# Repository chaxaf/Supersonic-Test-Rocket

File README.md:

# Hermes II Avionics Redesign

Semester project completed with the EPFL Rocket Team in 2022.

Hermes II is a compact avionics architecture developed for a small experimental rocket intended for validation flights and data generation. The project focused on redesigning the electronics of the original Hermes platform into a smaller, more modular system with telemetry, GPS, multiple sensor boards, and improved integration inside the rocket.

## Project summary

The avionics stack is built around one main PCB and three auxiliary PCBs placed in different parts of the rocket:

- **Main PCB** in the avionics bay
- **Nosecone PCB** for total pressure and wall temperature
- **Static port PCB** for static pressure and wall temperature
- **Load cell PCB** for thrust measurement signal conditioning

The design integrates:
- Teensy 3.5 microcontroller
- GPS
- XBee telemetry
- IMU and accelerometer
- pressure sensors
- thermocouple interfaces
- load cell instrumentation amplifier
- battery management and power regulation

## System overview

**Source in repository:** `docs/Hermes_Presentation.pptx`

## Main PCB

The main board had to fit inside a very constrained avionics bay while interfacing with the GPS, telemetry radio, IMU, pressure sensors, thermocouples, Altimax, Wildhorn sensor board, and auxiliary boards. It uses a 4-layer stack-up with dedicated ground and power planes.

## GPS layout constraints

One of the most layout-sensitive parts of the board was the GPS section, especially antenna routing and the controlled-impedance microstrip connection.

## Auxiliary PCBs

### Nosecone PCB
Measures total pressure and wall temperature.

### Static port PCB
Measures static pressure and wall temperature.

### Load cell PCB
Conditions the load cell signal used for thrust measurement.

## Main technical points

- Compact avionics redesign for a constrained rocket airframe
- Separation of avionics into one main PCB and three auxiliary PCBs
- Integration of telemetry and GPS
- Pressure, temperature, acceleration, and inertial sensing
- Load cell instrumentation for thrust measurements
- 4-layer PCB design under mechanical, thermal, and routing constraints
- Manufacturing through a combination of external PCB assembly and manual soldering

## Results

According to the final presentation, the following subsystems were functional during project testing:

- GPS worked outdoors
- telemetry radio worked
- thermocouples worked
- pressure sensors, IMU, and Altimax were functional
- the accelerometer worked after replacing a faulty capacitor

Main issues and remaining work included:

- power supply malfunction
- some MAX31855 thermocouple interfaces failed
- connector orientation errors that were later corrected
- remaining validation work for the load cell amplifier and some Wildhorn sensor software

See slides **“RESULTATS”** and **“CONCLUSION”** in `docs/Hermes_Presentation.pptx`.

## Repository structure

```text
Hermes-II-GitHub/
├── README.md
├── .gitignore
├── docs/
│   ├── Hermes_Presentation.pptx
│   └── report.pdf
├── images/
│   ├── rocket_overview.png
│   ├── avionics_bay.png
│   ├── system_block_diagram.png
│   ├── main_pcb_top.png
│   ├── main_pcb_bottom.png
│   ├── main_pcb_signal_routing.png
│   ├── main_pcb_power_planes.png
│   ├── gps_layout_guidelines.png
│   ├── gps_microstrip_stackup.png
│   ├── nosecone_board.png
│   ├── static_port_board.png
│   └── load_cell_board.png
└── hardware/
    ├── main_pcb/
    ├── nosecone_pcb/
    ├── static_port_pcb/
    └── load_cell_pcb/
```

## Opening the hardware files

The hardware design files are provided in KiCad project format. Open the corresponding `.kicad_pro` file in each hardware subfolder.

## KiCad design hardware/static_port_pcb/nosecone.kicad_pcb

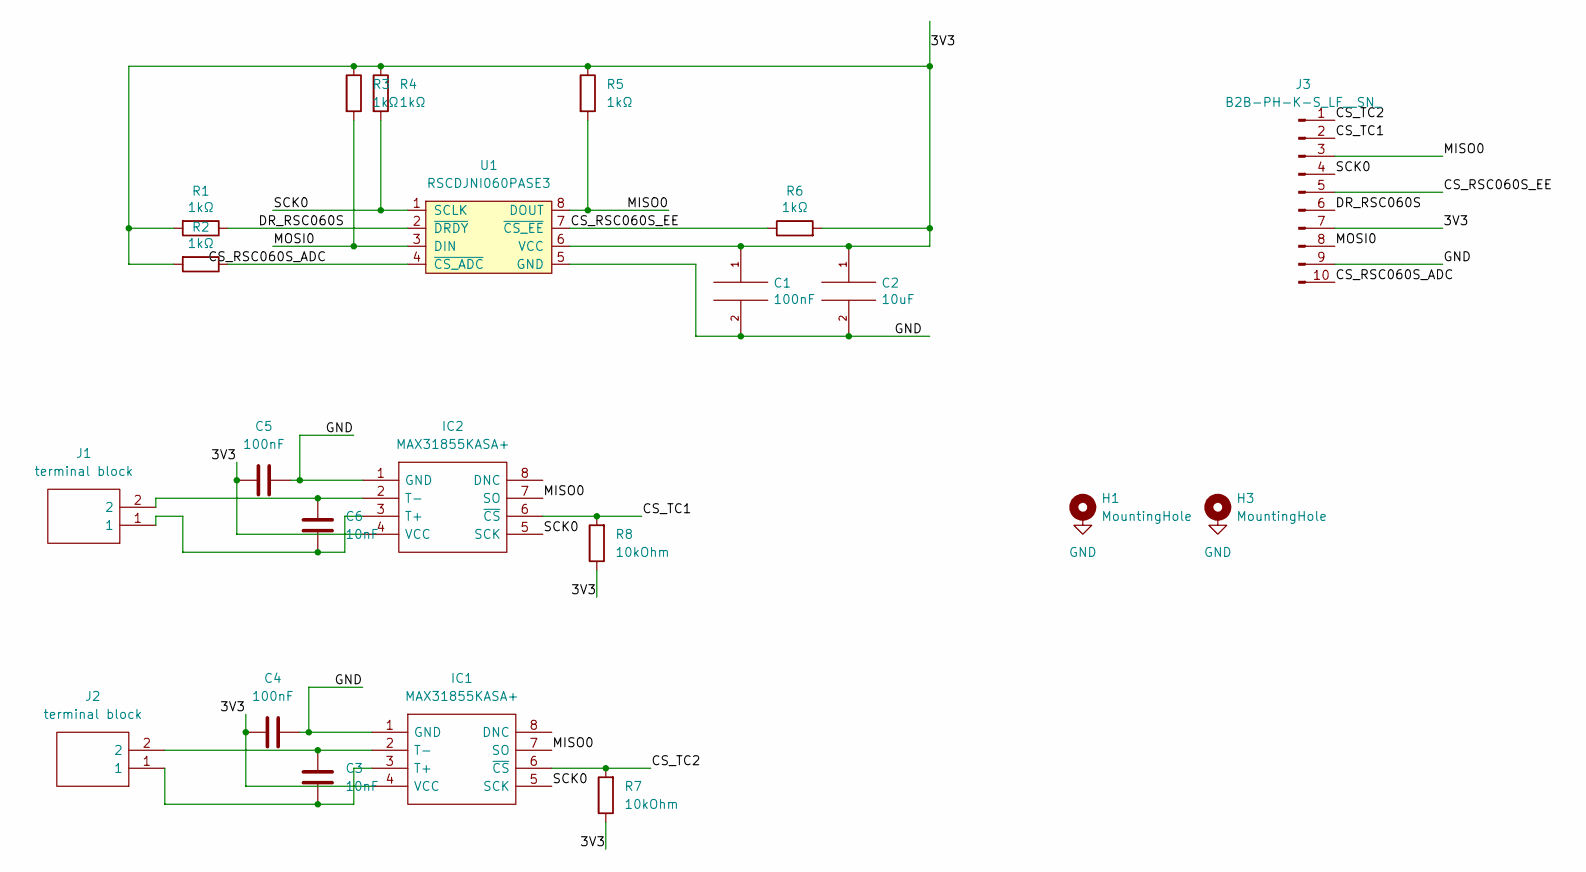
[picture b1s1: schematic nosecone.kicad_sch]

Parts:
C1, C4, C5: 100nF; C_0603_1608Metric
C2: 10uF; C_0603_1608Metric
C3, C6: 10nF; C_0603_1608Metric
H1, H3: MountingHole; MountingHole_2.2mm_M2
IC1, IC2: MAX31855KASA+; SOIC127P600X175-8N; Manufacturer_Part_Number MAX31855KASA+; Mouser Part Number 700-MAX31855KASA+
J1, J2: terminal block; Manufacturer_Part_Number 1725656; Mouser Part Number 651-1725656
J3: B2B-PH-K-S_LF__SN_; 57202G5205LF
R1, R2, R3, R4, R5, R6: 1kΩ; R_0603_1608Metric
R7, R8: 10kOhm; R_0603_1608Metric
U1: RSCDJNI060PASE3; DIP-8_W13.08mm

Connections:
/3V3: C1.1, C2.1, C4.2, C5.2, IC1.4 (VCC), IC2.4 (VCC), J3.7, R1.2, R2.2, R3.1, R4.1, R5.1, R6.2, R7.1, R8.1, U1.6 (VCC)
/CS_RSC060S_ADC: J3.10, R2.1, U1.4 (~CS_ADC)
/CS_RSC060S_EE: J3.5, R6.1, U1.7 (~CS_EE)
/CS_TC1: IC2.6 (~CS), J3.2, R8.2
/CS_TC2: IC1.6 (~CS), J3.1, R7.2
/DR_RSC060S: J3.6, R1.1, U1.2 (~DRDY)
/MISO0: IC1.7 (SO), IC2.7 (SO), J3.3, R5.2, U1.8 (DOUT)
/MOSI0: J3.8, R3.2, U1.3 (DIN)
/SCK0: IC1.5 (SCK), IC2.5 (SCK), J3.4, R4.2, U1.1 (SCLK)
GND: C1.2, C2.2, C4.1, C5.1, IC1.1 (GND), IC2.1 (GND), J3.9, U1.5 (GND)
unnamed: C3.1, IC1.3 (T+), J2.1
unnamed: C3.2, IC1.2 (T-), J2.2
unnamed: C6.1, IC2.3 (T+), J1.1
unnamed: C6.2, IC2.2 (T-), J1.2

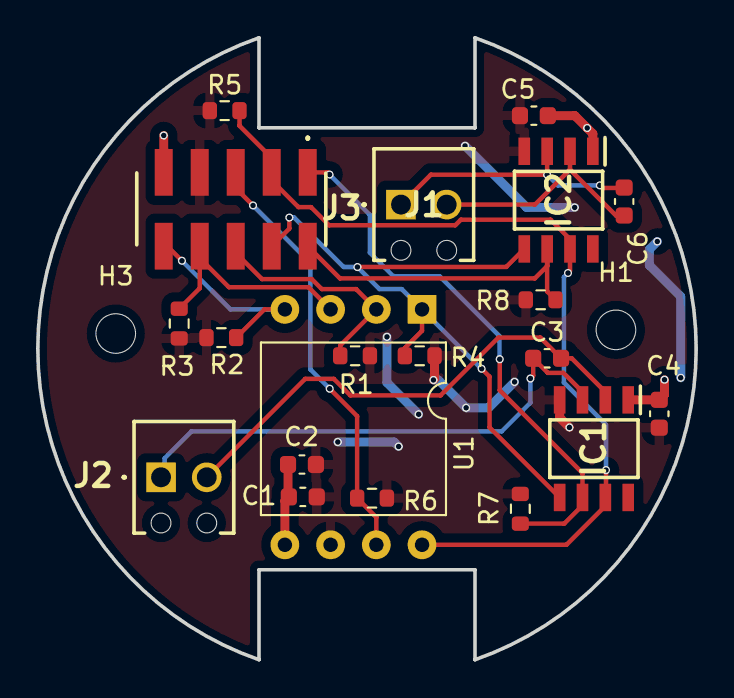
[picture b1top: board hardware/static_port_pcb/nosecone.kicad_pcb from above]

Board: 2 copper layers, 36.6 x 34.6 mm, 22 parts (0 on the bottom side), 14 nets.

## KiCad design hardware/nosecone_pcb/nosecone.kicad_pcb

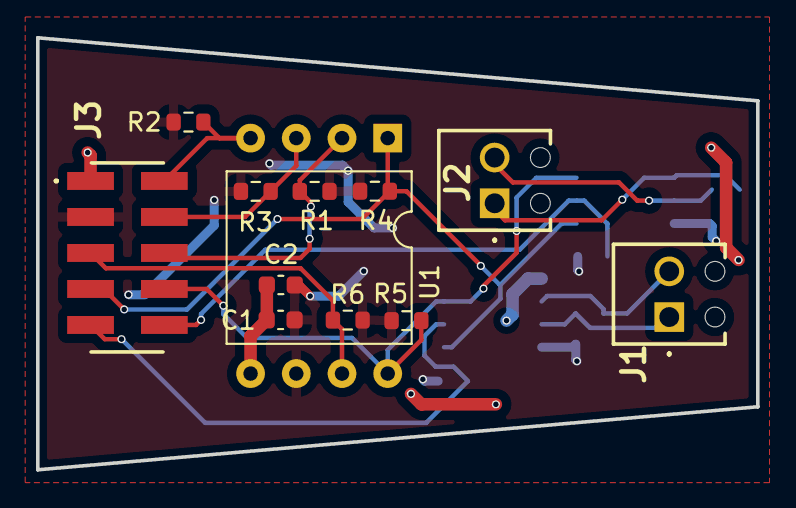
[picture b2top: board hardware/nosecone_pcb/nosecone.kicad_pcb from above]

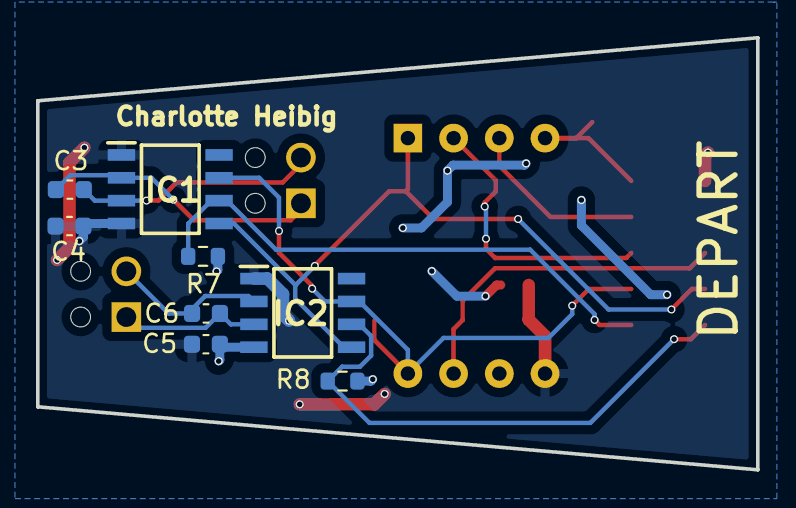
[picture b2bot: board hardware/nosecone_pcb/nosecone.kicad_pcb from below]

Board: 2 copper layers, 40.0 x 24.0 mm, 20 parts (8 on the bottom side), 14 nets.

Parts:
C1, C4, C5: 100nF; C_0603_1608Metric
C2: 10uF; C_0603_1608Metric
C3, C6: 10nF; C_0603_1608Metric
IC1, IC2: MAX31855KASA+; SOIC127P600X175-8N
J1, J2: 1725656
J3: B2B-PH-K-S_LF__SN_; 57202G5205LF
R1, R2, R3, R4, R5, R6: 1kΩ; R_0603_1608Metric
R7, R8: 10kOhm; R_0603_1608Metric
U1: RSCDJNI060PASE3; DIP-8_W13.08mm

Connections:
/3V3: C1.1, C2.1, C5.2, IC2.4 (VCC), J3.3, R1.2, R2.2, R3.1, R4.1, R5.1, R6.2, R7.1, R8.1, U1.6 (VCC)
/CS_RSC060S_ADC: J3.2, R2.1, U1.4 (~CS_ADC)
/CS_RSC060S_EE: J3.5, R6.1, U1.7 (~CS_EE)
/CS_TC3: IC2.6 (~CS), J3.9, R8.2
/CS_TC4: IC1.6 (~CS), J3.10, R7.2
/DR_RSC060S: J3.6, R1.1, U1.2 (~DRDY)
/GND: C1.2, C2.2, C4.1, C4.2, C5.1, IC1.1 (GND), IC1.4 (VCC), IC2.1 (GND), J3.1, U1.5 (GND)
/MISO0: IC1.7 (SO), IC2.7 (SO), J3.8, R5.2, U1.8 (DOUT)
/MOSI0: J3.4, R3.2, U1.3 (DIN)
/SCK0: IC1.5 (SCK), IC2.5 (SCK), J3.7, R4.2, U1.1 (SCLK)
unnamed: C3.1, IC1.3 (T+), J2.2
unnamed: C3.2, IC1.2 (T-), J2.1
unnamed: C6.1, IC2.3 (T+), J1.1
unnamed: C6.2, IC2.2 (T-), J1.2

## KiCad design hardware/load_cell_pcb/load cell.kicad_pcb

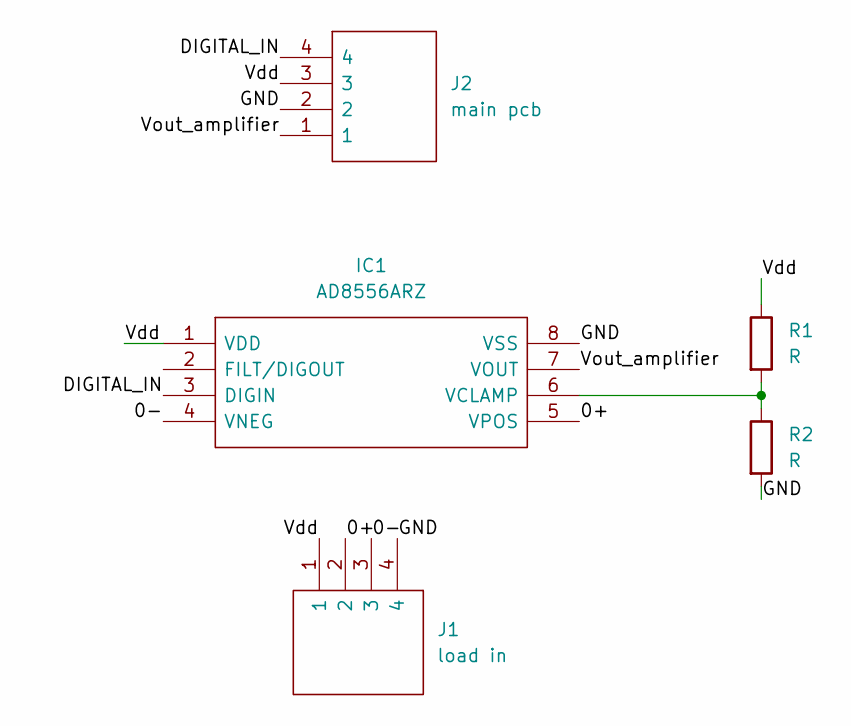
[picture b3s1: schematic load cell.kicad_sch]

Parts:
IC1: AD8556ARZ; SOIC127P600X175-8N; Manufacturer_Part_Number AD8556ARZ; Mouser Part Number 584-AD8556ARZ
J1: load in; 17345984; Manufacturer_Part_Number 1734598-4; Mouser Part Number 571-1734598-4
J2: main pcb; load to main; Manufacturer_Part_Number 1734598-4; Mouser Part Number 571-1734598-4
R1, R2: R; R_0603_1608Metric

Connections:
/0+: IC1.5 (VPOS), J1.2
/0-: IC1.4 (VNEG), J1.3
/DIGITAL_IN: IC1.3 (DIGIN), J2.4
/GND: IC1.8 (VSS), J1.4, J2.2, R2.2
/Vdd: IC1.1 (VDD), J1.1, J2.3, R1.1
/Vout_amplifier: IC1.7 (VOUT), J2.1
unnamed: IC1.6 (VCLAMP), R1.2, R2.1

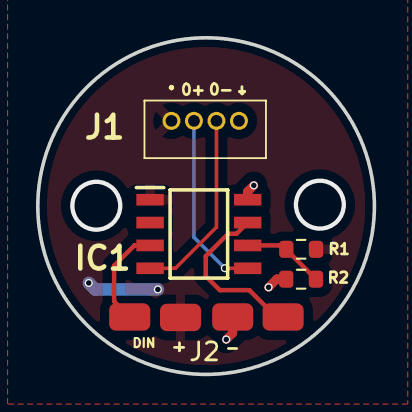
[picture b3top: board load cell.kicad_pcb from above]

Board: 2 copper layers, 18.7 x 18.7 mm, 5 parts (0 on the bottom side), 7 nets.

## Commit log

2026-03-30 Create reporti
2026-03-31 Create delete
